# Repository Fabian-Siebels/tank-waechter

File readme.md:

# tank-waechter
#### by Fabian Siebels | 10.2020

### Anforderungen

Überwachung folgender Funktionen:
- Überwachung der Milchtemperatur mit Alarmierung für den Michlerzeuger
- Überwachung des Rührwerks mit Alarmierung für den Milcherzeuger
- Überwachung der Mindest-Reinigungstemperatur
- Speicherung von Fehlermeldungen für mind. 30 Tage
- "Nicht laden"-Funktion

Sobald die Milch die in der Milchlieferung beschriebenden Qualitätsanforderungen nicht mehr erfüllt, muss der Tankwächter ein eindeutig wahrnehmbares optisches oder akustisches Signal abgeben ("Nicht laden" Funktion).

Die "Nicht laden" Funktion ist wie folgt definiert:
- Milchtemperatur mehr als 600 Minuten über 13 °C
- Milchtemperatur mehr als 360 Minuten über 16 °C
- Milchtemperatur mehr als 300 Minuten über 28 °C
- Netzwerkstörung mehr als 300 Minuten

## Installation

1.  1Wire aktivieren

```
sudo modprobe wire
sudo modprobe w1-gpio
sudo modprobe w1-therm
```

2. Für immer aktivieren
```
sudo nano /boot/config.txt

# 1-Wire Temperatursensor, Daten an Pin 4
dtoverlay=w1-gpio
gpiopin=4
```

#### Display

i2C aktivieren
sudo apt-get install python-smbus
sudo apt-get install i2c-tool
i2cdetect -y 1      <--- x27

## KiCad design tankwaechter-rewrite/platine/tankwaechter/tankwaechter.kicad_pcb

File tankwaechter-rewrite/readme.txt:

WEMOS D1

SD Karte Pins
D5
D6
D7
D8

Display + DS18B12
D1
D2

Spannungsmessung
A0

Quittieren
RX

Lichtsensor1
D3

Lichtsensor2
D4

Summer
D0

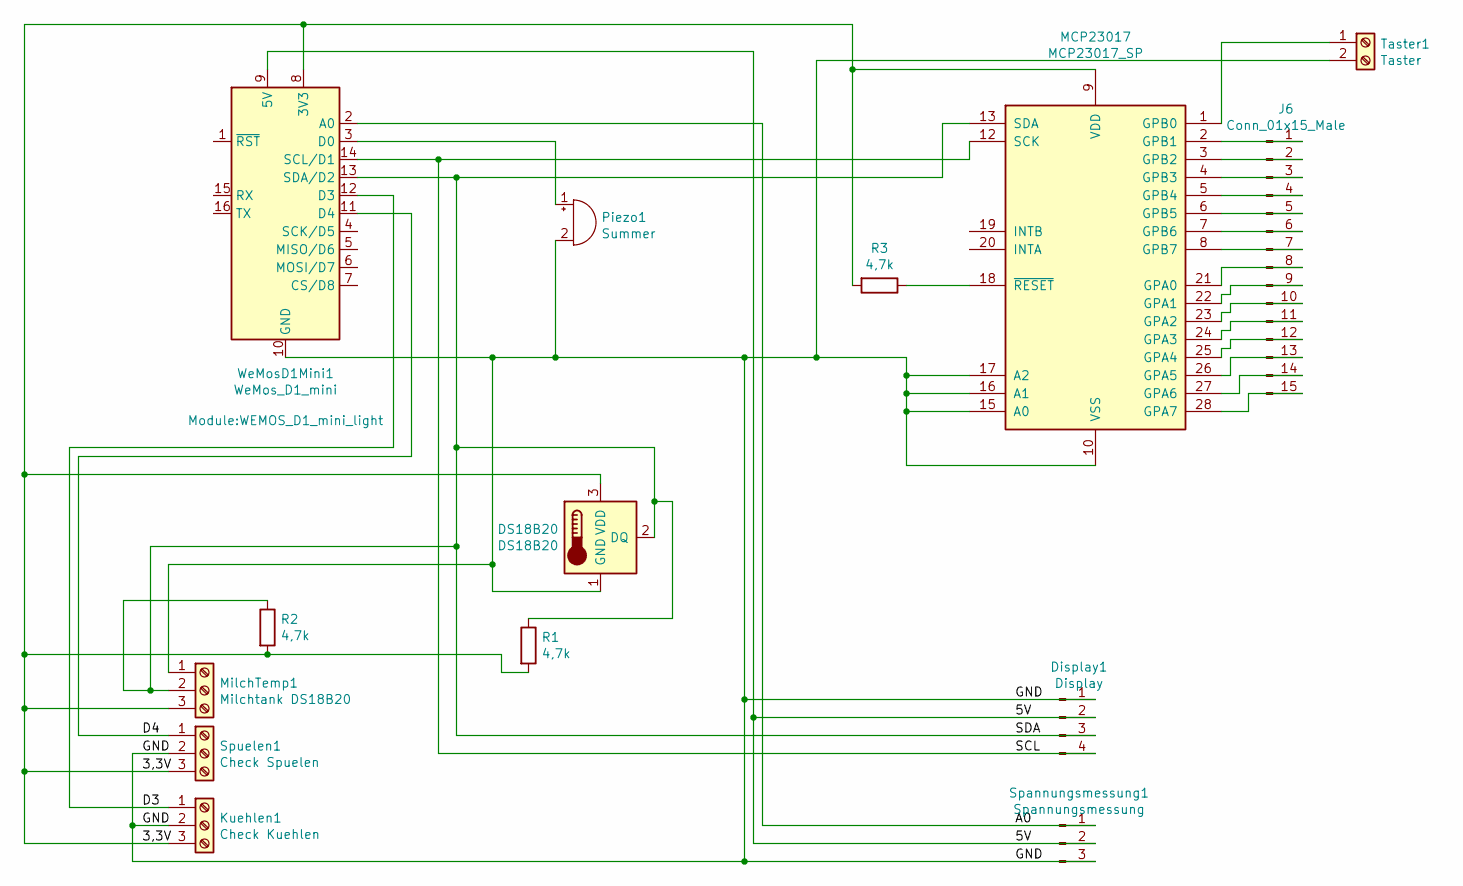
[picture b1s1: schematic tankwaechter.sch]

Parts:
DS18B20: DS18B20; TO-92_Inline
Display1: Display; JST_EH_B4B-EH-A_1x04_P2.50mm_Vertical
J6: Conn_01x15_Male; JST_EH_B15B-EH-A_1x15_P2.50mm_Vertical
Kuehlen1: Check Kuehlen; TerminalBlock_bornier-3_P5.08mm
MCP23017: MCP23017_SP; DIP-28_W7.62mm
MilchTemp1: Milchtank DS18B20; TerminalBlock_bornier-3_P5.08mm
Piezo1: Summer; Buzzer_12x9.5RM7.6
R1, R2, R3: 4,7k; R_Axial_DIN0204_L3.6mm_D1.6mm_P7.62mm_Horizontal
Spannungsmessung1: Spannungsmessung; JST_EH_B3B-EH-A_1x03_P2.50mm_Vertical
Spuelen1: Check Spuelen; TerminalBlock_bornier-3_P5.08mm
Taster1: Taster; TerminalBlock_bornier-2_P5.08mm
WeMosD1Mini1: WeMos_D1_mini; WEMOS_D1_mini_light

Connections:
/3,3V: DS18B20.3 (VDD), Kuehlen1.3, MCP23017.9 (VDD), MilchTemp1.3, R1.2, R2.2, R3.2, Spuelen1.3, WeMosD1Mini1.8 (3V3)
/5V: Display1.2, Spannungsmessung1.2, WeMosD1Mini1.9 (5V)
/A0: Spannungsmessung1.1, WeMosD1Mini1.2 (A0)
/D3: Kuehlen1.1, WeMosD1Mini1.12 (D3)
/D4: Spuelen1.1, WeMosD1Mini1.11 (D4)
/GND: DS18B20.1 (GND), Display1.1, Kuehlen1.2, MCP23017.10 (VSS), MCP23017.15 (A0), MCP23017.16 (A1), MCP23017.17 (A2), MilchTemp1.1, Piezo1.2 (+), Spannungsmessung1.3, Spuelen1.2, Taster1.2, WeMosD1Mini1.10 (GND)
/SCL: Display1.4, MCP23017.12 (SCK), WeMosD1Mini1.14 (SCL/D1)
/SDA: DS18B20.2 (DQ), Display1.3, MCP23017.13 (SDA), MilchTemp1.2, R1.1, R2.1, WeMosD1Mini1.13 (SDA/D2)
unnamed: J6.1, MCP23017.2 (GPB1)
unnamed: J6.2, MCP23017.3 (GPB2)
unnamed: J6.3, MCP23017.4 (GPB3)
unnamed: J6.4, MCP23017.5 (GPB4)
unnamed: J6.5, MCP23017.6 (GPB5)
unnamed: J6.6, MCP23017.7 (GPB6)
unnamed: J6.7, MCP23017.8 (GPB7)
unnamed: J6.8, MCP23017.21 (GPA0)
unnamed: J6.9, MCP23017.22 (GPA1)
unnamed: J6.10, MCP23017.23 (GPA2)
unnamed: J6.11, MCP23017.24 (GPA3)
unnamed: J6.12, MCP23017.25 (GPA4)
unnamed: J6.13, MCP23017.26 (GPA5)
unnamed: J6.14, MCP23017.27 (GPA6)
unnamed: J6.15, MCP23017.28 (GPA7)
unnamed: MCP23017.1 (GPB0), Taster1.1
unnamed: MCP23017.18 (~RESET~), R3.1
unnamed: Piezo1.1 (-), WeMosD1Mini1.3 (D0)

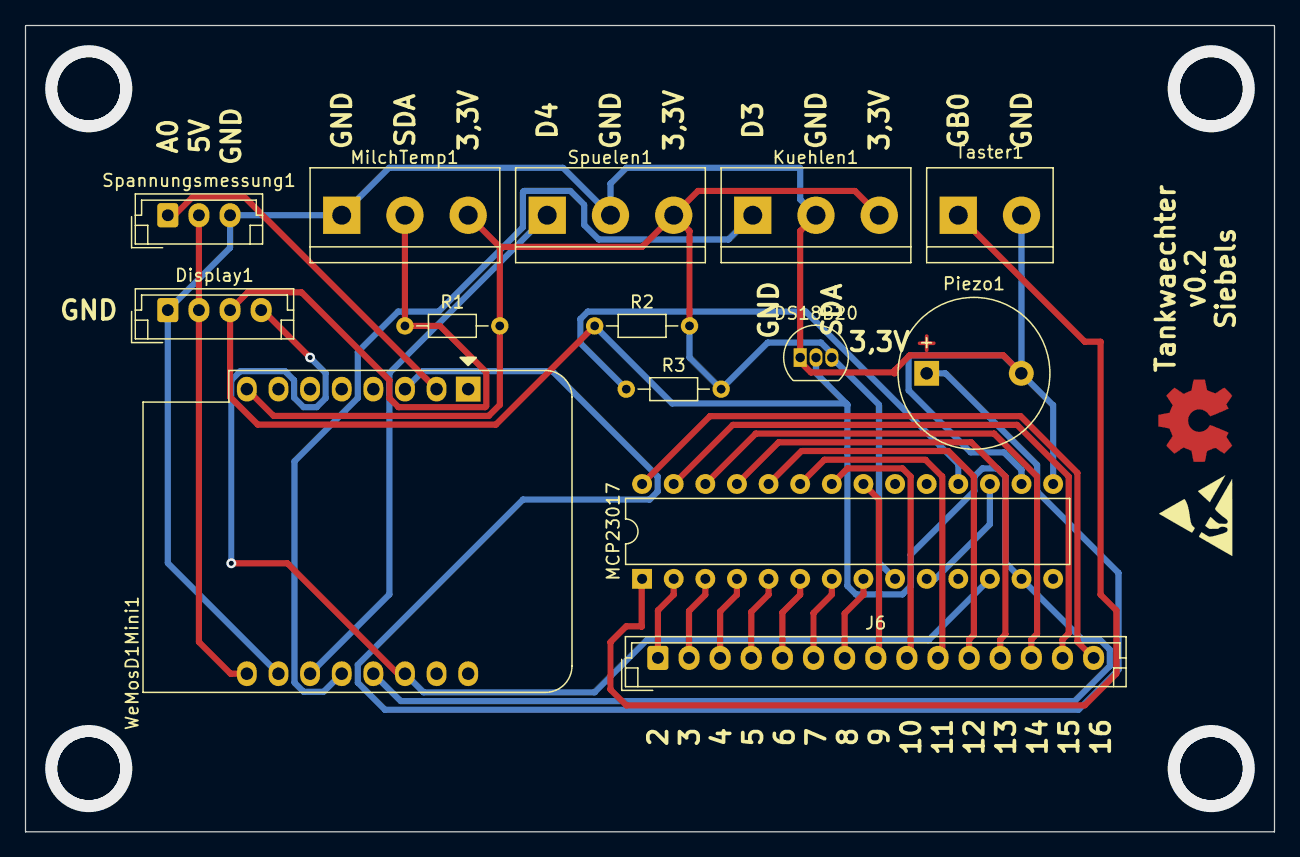
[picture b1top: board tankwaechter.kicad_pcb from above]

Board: 2 copper layers, 100.3 x 64.8 mm, 14 parts (0 on the bottom side), 26 nets.

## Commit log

2020-10-08 init
2020-10-21 algo clear
2020-10-24 influx +
2020-10-24 sensorparser und query
2020-10-25 telegram error
2020-10-26 ip ~ catch bei abfragen
2020-10-26 bugfix readme akt
2020-10-26 gruppenfunkt
2020-10-27 nodemon
2020-10-27 userlogin
2020-10-27 login per pin mit dublikatsprüfung
2020-10-28 check 4 groups
2020-10-28 msg 2 multiuser
2020-10-28 ds18b20 integration
2020-10-28 /temp
2020-10-28 min/max temp
2020-10-28 min/max tage nach eingabe
2020-10-29 var bugfix
2020-10-29 display test
2020-10-29 verschieben
2020-10-29 bugfix
2020-10-29 display
2020-10-29 sedg
2020-10-29 display temp
2020-10-30 webserver und api hinzugefügt
2020-10-31 setInterval durch Cron ersetzt
2020-11-08 website time hinzu
2020-11-08 farben vom chart angepasst
2020-11-08 start checktemp
2021-03-05 arduino funkt version
